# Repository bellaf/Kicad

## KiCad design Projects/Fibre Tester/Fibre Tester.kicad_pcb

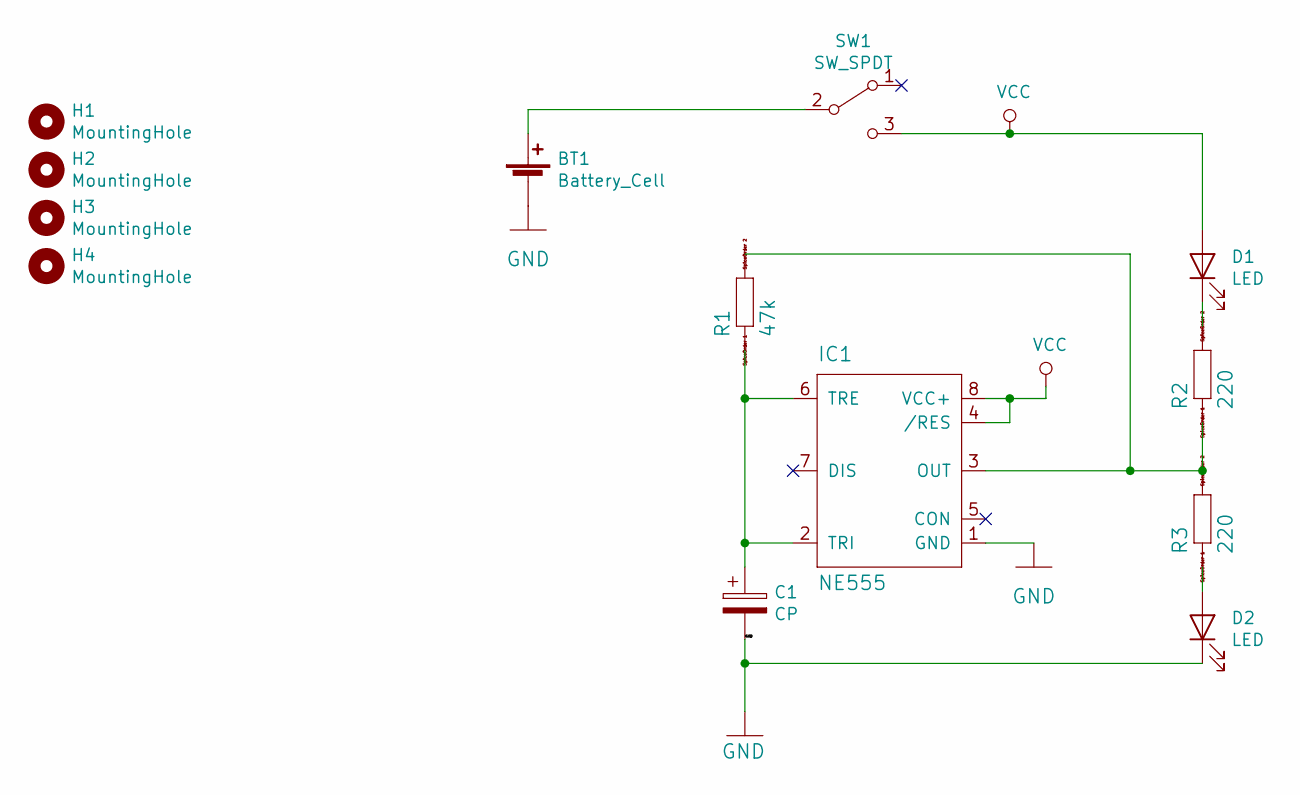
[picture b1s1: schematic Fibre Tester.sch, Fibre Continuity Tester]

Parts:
BT1: Battery_Cell; PinSocket_1x02_P2.54mm_Vertical
C1: CP; CP_Radial_D6.3mm_P2.50mm
D1, D2: LED; LED_D5.0mm_Clear
H1, H2, H3, H4: MountingHole; MountingHole_2.5mm
IC1: NE555; DIP-8_W7.62mm
R1: 47k; R_Axial_DIN0207_L6.3mm_D2.5mm_P10.16mm_Horizontal
R2, R3: 220; R_Axial_DIN0207_L6.3mm_D2.5mm_P10.16mm_Horizontal
SW1: SW_SPDT; SW_Slide_angle_SPDT_TB

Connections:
GND: BT1.2 (-), C1.2, D2.1 (K), IC1.1 (GND)
unnamed: BT1.1 (+), SW1.2 (B)
unnamed: C1.1, IC1.2 (TRI), IC1.6 (TRE), R1.1
unnamed: D1.1 (K), R2.2
unnamed: D2.2 (A), R3.1
unnamed: IC1.3 (OUT), R1.2, R2.1, R3.2
VCC: D1.2 (A), IC1.4 (/RES), IC1.8 (VCC+), SW1.3 (C)

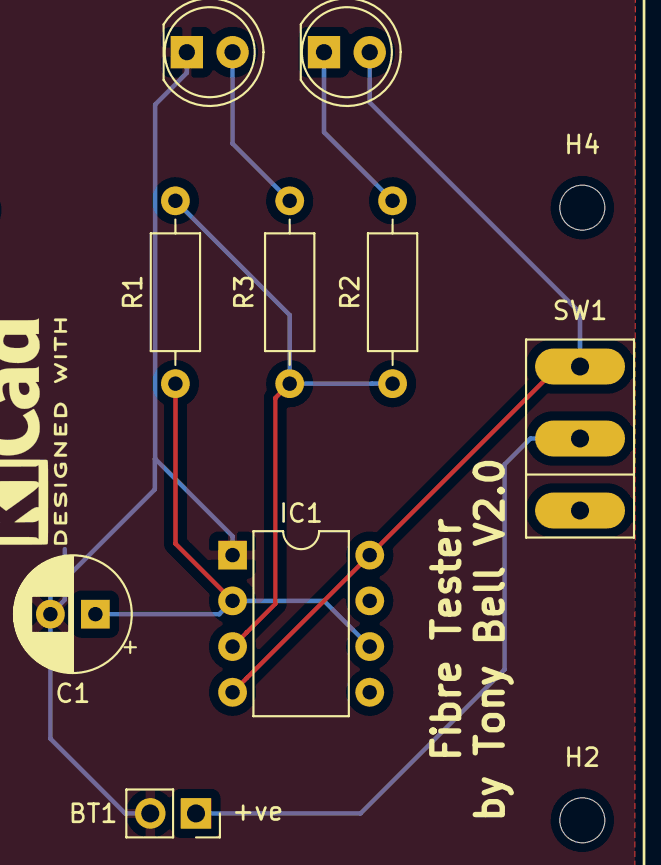
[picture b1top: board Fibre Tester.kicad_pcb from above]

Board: 2 copper layers, 13 parts (0 on the bottom side), 7 nets.

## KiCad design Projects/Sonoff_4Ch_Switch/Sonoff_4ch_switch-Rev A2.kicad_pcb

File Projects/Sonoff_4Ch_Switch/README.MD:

Sonoff inspired, 4Ch Switch using Tasmota Firmware

Notes on implementation

So, configure Tasmota as a HUE Bridge (Multi Device)

Then configure the module as a GENERIC (Type18) module for the Wemos.

Then in the module config, set the following options:

D3 GPIO0: 17 Button1	
TX GPIO1: 00 None	
D4 GPIO2: 18 Button2 	
RX GPIO3: 00 None
D2 GPIO4: 23 Relay3
D1 GPIO5: 22 Relay2 	
D6 GPIO12: 21 Relay1
D7 GPIO13: 00 None
D5 GPIO14: 19 Button3
D8 GPIO15: 24 Relay4
D0 GPIO16: 20 Button4

Thats it, set Alexa to discover it all and bingo!
 	
Adding a DS1820B Onewire connection as well to make the unit versatile......
using GPIO13 on D7 for this..

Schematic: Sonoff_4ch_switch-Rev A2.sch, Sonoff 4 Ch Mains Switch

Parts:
C1: 10uF; CP_Elec_6.3x9.9
C2: 22uF; CP_Elec_6.3x9.9
D9: LED; LED_0805_HandSoldering
F1: Fuse 5A; Fuseholder5x20_horiz_SemiClosed_Casing10x25mm
J1: Barrel_Jack_Switch; BARREL_JACK
J2: Live; TerminalBlock_RND_205-00004_1x05_P5.00mm_Horizontal
J3: Neutrals; TerminalBlock_RND_205-00004_1x05_P5.00mm_Horizontal
J4: Earths; TerminalBlock_RND_205-00004_1x05_P5.00mm_Horizontal
J5: Conn_01x03_Male; PinHeader_1x03_P2.54mm_Vertical
MH1, MH2, MH3, MH4: MountingHole; MountingHole_3mm_Pad
R17, R18, R19, R20, R21: 1K; R_0805_HandSoldering
R22: 4.7K; R_0805_HandSoldering
S1, S2, S3, S4: PTS645SM43SMTR92_LFS; Switch_Tactile_SMD_6x6mm_PTS645; MPN PTS645SM43SMTR92 LFS; Digi-Key_PN CKN9112CT-ND
TP1: 5V; Measurement_Point_Round-SMD-Pad_Small
TP2: 3.3V; TestPoint_Pad_D2.0mm
TP3: GND; Measurement_Point_Round-SMD-Pad_Small
U1: AP1117-50; SOT-223-3_TabPin2
U2: Wemos_D1_Mini_wide; Wemos_D1_mini_board-flipped

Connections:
+3V3: J5.3, R18.1, R19.1, R20.1, R21.1, R22.1, TP2.1, U2.16
+5V: C2.1, R17.1, TP1.1, U1.2 (VO), U2.1; also elsewhere on the board
/DC_IN: C1.1, J1.1, U1.3 (VI)
AC: F1.1, J2.1
Earth: J4.1, J4.2, J4.3, J4.4, J4.5
GND: C1.2, C2.2, D9.1, J1.2, J1.3, J5.1, S1.1, S1.2, S2.1, S2.2, S3.1, S3.2, S4.1, S4.2, TP3.1, U1.1 (GND), U2.2; also elsewhere on the board
L1: J2.2; also elsewhere on the board
L2: J2.3; also elsewhere on the board
L3: J2.4; also elsewhere on the board
L4: J2.5; also elsewhere on the board
LineIN: F1.2; also elsewhere on the board
unnamed: D9.2, R17.2
unnamed: R18.2, S1.3
unnamed: R19.2, S2.3
unnamed: R20.2, S3.3
unnamed: R21.2, S4.3
Neutral: J3.1, J3.2, J3.3, J3.4, J3.5
OneWire: J5.2, R22.2, U2.14
Relay1: U2.13; also elsewhere on the board
Relay2: U2.6; also elsewhere on the board
Relay3: U2.5; also elsewhere on the board
Relay4: U2.15; also elsewhere on the board
SW0: S1.4, U2.4
SW2: S2.4, U2.3
SW14: S3.4, U2.11
SW16: S4.4, U2.12

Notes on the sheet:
PSU: 6V - 12V DC IN (5V Output)
Mains Terminal Blocks
Design notes for rev A2: 1. Add a GND TP, with a pin(?) - Done 2. No Reverse polarity protection 3. Do away with the Regulator? Run it from 5V Power bricks? 4. Redesign the layout with 0805 components! (0603 too small) - Done 5. If keeping the regulator, re-engineer the copper pad for 5V, needs to 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

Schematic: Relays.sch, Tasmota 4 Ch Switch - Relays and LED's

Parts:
D1, D2, D3, D4: 1N4148; D_SOD-123
D5, D6, D7, D8: LED; LED_0805_HandSoldering
K1, K2, K3, K4: G5LE-1; Relay_SPDT_Omron-G5LE-1
Q1, Q2, Q3, Q4, Q5, Q6, Q7, Q8: 2N7002; SOT-23
R1, R3, R5, R7, R9, R10, R11, R12, R13, R14, R15, R16: 1K; R_0805_HandSoldering
R2, R4, R6, R8: 10K; R_0805_HandSoldering

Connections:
+5V: D1.1, D2.1, D3.1, D4.1, D5.2, D6.2, D7.2, D8.2, K1.5, K2.5, K3.5, K4.5; also elsewhere on the board
GND: Q1.2 (S), Q2.2 (S), Q3.2 (S), Q4.2 (S), Q5.2 (S), Q6.2 (S), Q7.2 (S), Q8.2 (S), R2.1, R4.1, R6.1, R8.1; also elsewhere on the board
L1: K1.3; also elsewhere on the board
L2: K2.3; also elsewhere on the board
L3: K3.3; also elsewhere on the board
L4: K4.3; also elsewhere on the board
LineIN: K1.1, K2.1, K3.1, K4.1; also elsewhere on the board
unnamed: D1.2, K1.2, Q1.3 (D)
unnamed: D2.2, K2.2, Q2.3 (D)
unnamed: D3.2, K3.2, Q3.3 (D)
unnamed: D4.2, K4.2, Q4.3 (D)
unnamed: D5.1, R10.2
unnamed: D6.1, R12.2
unnamed: D7.1, R14.2
unnamed: D8.1, R16.2
unnamed: Q1.1 (G), R1.1, R2.2
unnamed: Q2.1 (G), R3.1, R4.2
unnamed: Q3.1 (G), R5.1, R6.2
unnamed: Q4.1 (G), R7.1, R8.2
unnamed: Q5.1 (G), R9.1
unnamed: Q5.3 (D), R10.1
unnamed: Q6.1 (G), R11.1
unnamed: Q6.3 (D), R12.1
unnamed: Q7.1 (G), R13.1
unnamed: Q7.3 (D), R14.1
unnamed: Q8.1 (G), R15.1
unnamed: Q8.3 (D), R16.1
Relay1: R1.2, R9.2; also elsewhere on the board
Relay2: R3.2, R11.2; also elsewhere on the board
Relay3: R5.2, R13.2; also elsewhere on the board
Relay4: R7.2, R15.2; also elsewhere on the board

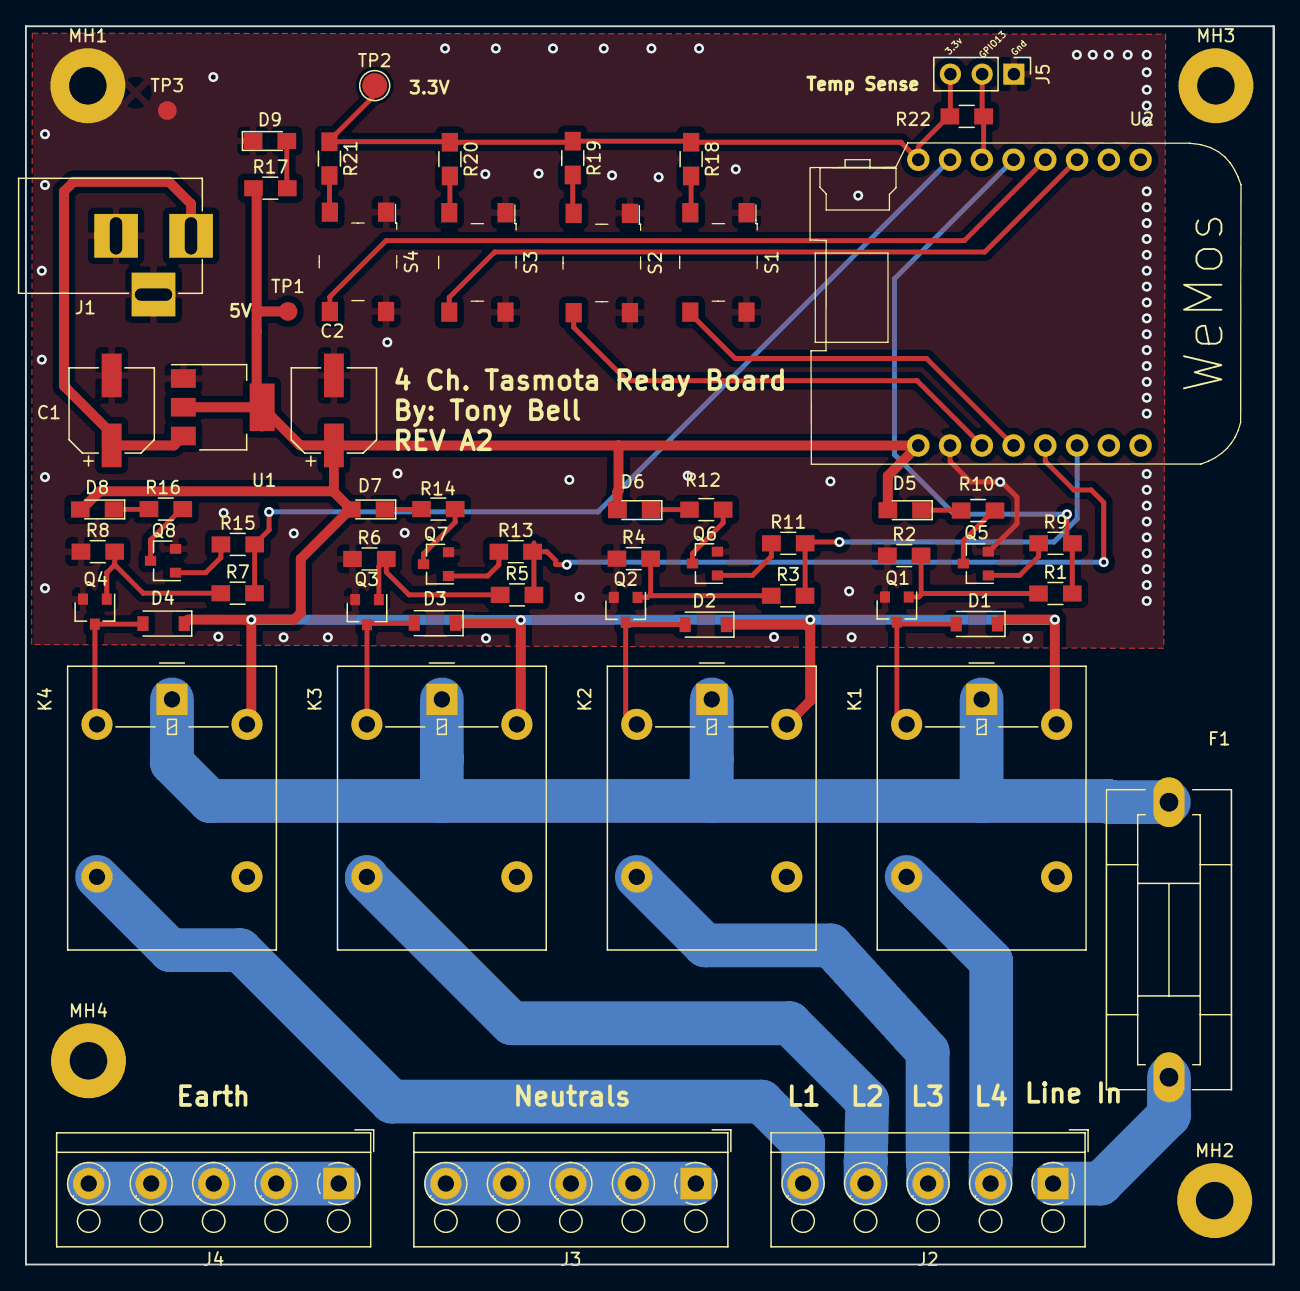
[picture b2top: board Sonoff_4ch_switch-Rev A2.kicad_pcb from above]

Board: 2 copper layers, 99.8 x 99.1 mm, 64 parts (0 on the bottom side), 46 nets.

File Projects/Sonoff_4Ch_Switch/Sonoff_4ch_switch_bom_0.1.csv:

Component,Description,Part,References,Value,Footprint,Quantity Per PCB,Datasheet,Category,Status,Family,MPN,Digi-Key_PN,DK_Datasheet_Link,DK_Detail_Page,Manufacturer
1,Polarised capacitor,CP,C1,10uF,CP_Elec_6.3x9.9,1,,,,,,,,,
2,Polarised capacitor,CP,C2,22uF,CP_Elec_6.3x9.9,1,,,,,,,,,
3,Diode,D,D1 D2 D3 D4,1N4148,D_SOD-123,4,~,,,,,,,,
4,LED generic,LED,D5 D6 D7 D8 D9,LED,LED_0603_HandSoldering,5,~,,,,,,,,
5,"Fuse, generic",Fuse,F1,Fuse 5A,Fuseholder5x20_horiz_SemiClosed_Casing10x25mm,1,~,,,,,,,,
6,DC Barrel Jack with an internal switch,Barrel_Jack_Switch,J1,Barrel_Jack_Switch,BARREL_JACK,1,,,,,,,,,
7,"Generic connector, single row, 01x03, script generated (kicad-library-utils/schlib/autogen/connector/)",Conn_01x03_Male,J5,Conn_01x03_Male,PinHeader_1x03_P2.54mm_Vertical,1,~,,,,,,,,
8,"Generic screw terminal, single row, 01x05, script generated (kicad-library-utils/schlib/autogen/connector/)",Screw_Terminal_01x05,J4,Earths,TerminalBlock_RND_205-00004_1x05_P5.00mm_Horizontal,1,~,,,,,,,,
9,"Generic screw terminal, single row, 01x05, script generated (kicad-library-utils/schlib/autogen/connector/)",Screw_Terminal_01x05,J2,Live,TerminalBlock_RND_205-00004_1x05_P5.00mm_Horizontal,1,~,,,,,,,,
10,"Generic screw terminal, single row, 01x05, script generated (kicad-library-utils/schlib/autogen/connector/)",Screw_Terminal_01x05,J3,Neutrals,TerminalBlock_RND_205-00004_1x05_P5.00mm_Horizontal,1,~,,,,,,,,
11,"Omron G5LE relay, Miniature Single Pole, SPDT, 10A",G5LE-1,K1 K2 K3 K4,G5LE-1,Relay_SPDT_Omron-G5LE-1,4,http://www.omron.com/ecb/products/pdf/en-g5le.pdf,,,,,,,,
12,"50V Vds, 0.22A Id, N-channel MOSFET, SOT-23",2N7002,Q1 Q2 Q3 Q4 Q5 Q6 Q7 Q8,2N7002,SOT-23,8,https://www.fairchildsemi.com/datasheets/2N/2N7002.pdf,,,,,,,,
13,Resistor,R,R2 R4 R6 R8,10K,R_0603_1608Metric_Pad1.05x0.95mm_HandSolder,4,~,,,,,,,,
14,Resistor,R,R1 R3 R5 R7 R9 R10 R11 R12 R13 R14 R15 R16 R17 R18 R19 R20 R21,1K,R_0603_1608Metric_Pad1.05x0.95mm_HandSolder,17,~,,,,,,,,
15,Resistor,R,R22,4.7K,R_0603_1608Metric_Pad1.05x0.95mm_HandSolder,1,~,,,,,,,,
16,SWITCH TACTILE SPST-NO 0.05A 12V,PTS645SM43SMTR92_LFS,S1 S2 S3 S4,PTS645SM43SMTR92_LFS,Switch_Tactile_SMD_6x6mm_PTS645,4,https://www.ckswitches.com/media/1471/pts645.pdf,Switches,Active,Tactile Switches,PTS645SM43SMTR92 LFS,CKN9112CT-ND,https://www.ckswitches.com/media/1471/pts645.pdf,/product-detail/en/c-k/PTS645SM43SMTR92-LFS/CKN9112CT-ND/1146934,C&K
17,1A LDO 5.0V Fixed output,AP1117-50,U1,AP1117-50,SOT-223-3_TabPin2,1,http://www.diodes.com/datasheets/AP1117.pdf,,,,,,,,
18,Wemos D1 Mini with GPIO ports,Wemos_D1_Mini_wide,U2,Wemos_D1_Mini_wide,,1,,,,,,,,,





Component Groups:,18
Component Count:,57
Fitted Components:,57
Number of PCBs:,1
Total components:,57
Schematic Version:,0.1
Schematic Date:,
BoM Date:,08/08/2018 09:17:03
Schematic Source:,C:\Users\BELLAF\Documents\Personal\Electronics Projects\Kicad\Projects\Sonoff_4Ch_Switch\Sonoff_4ch_switch.sch
KiCad Version:,Eeschema (5.0.0)

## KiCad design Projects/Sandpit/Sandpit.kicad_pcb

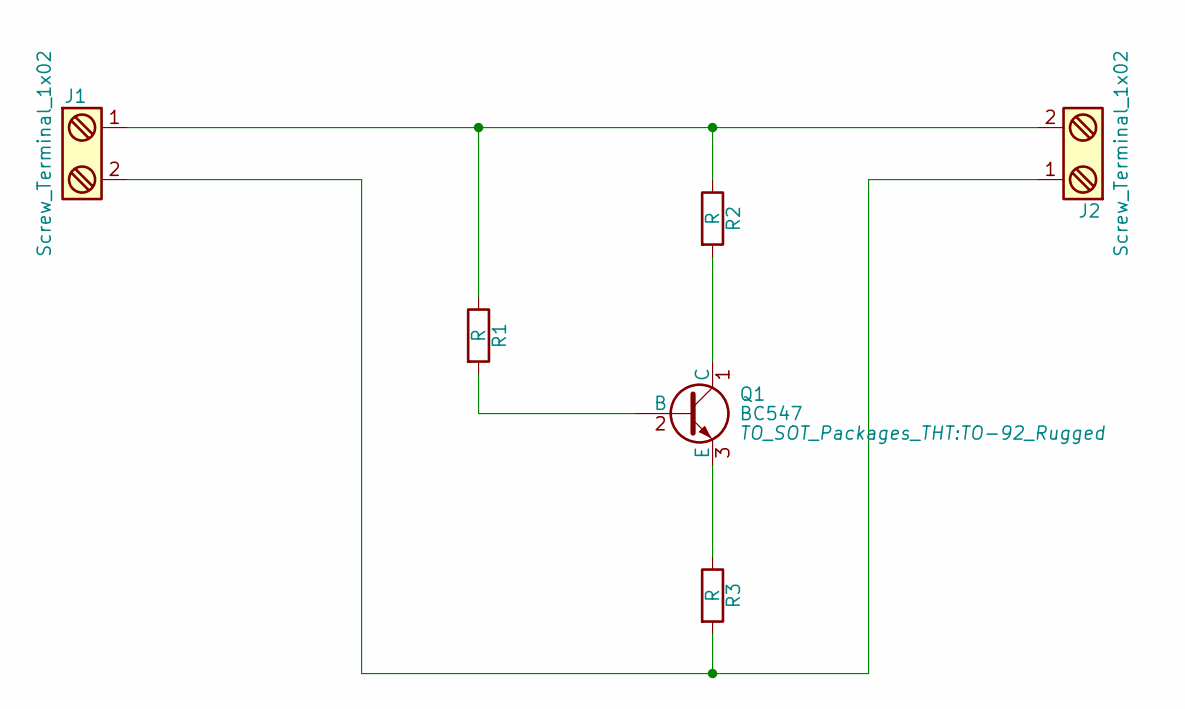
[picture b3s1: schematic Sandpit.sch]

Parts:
J1, J2: Screw_Terminal_1x02; Screw_Terminal_1x02_5mm
Q1: BC547; TO-92_Rugged
R1, R2, R3: R; R_Axial_DIN0207_L6.3mm_D2.5mm_P15.24mm_Horizontal

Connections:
unnamed: J1.1, J2.2, R1.1, R2.1
unnamed: J1.2, J2.1, R3.2
unnamed: Q1.1 (C), R2.2
unnamed: Q1.2 (B), R1.2
unnamed: Q1.3 (E), R3.1

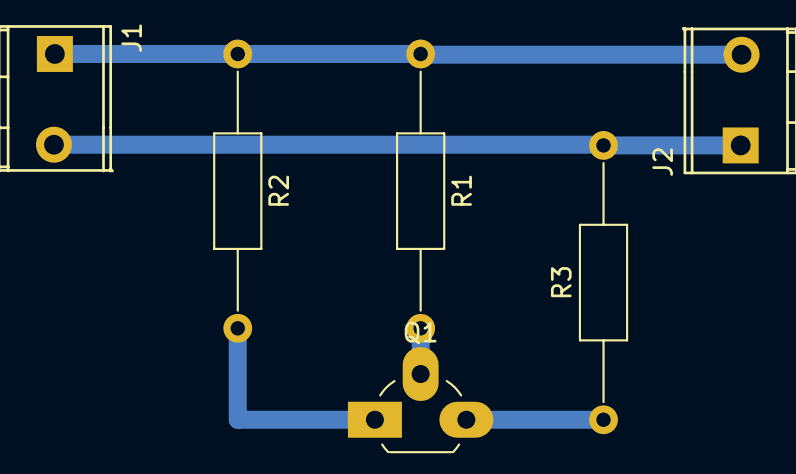
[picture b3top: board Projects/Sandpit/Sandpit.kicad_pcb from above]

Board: 2 copper layers, 6 parts (0 on the bottom side), 5 nets.

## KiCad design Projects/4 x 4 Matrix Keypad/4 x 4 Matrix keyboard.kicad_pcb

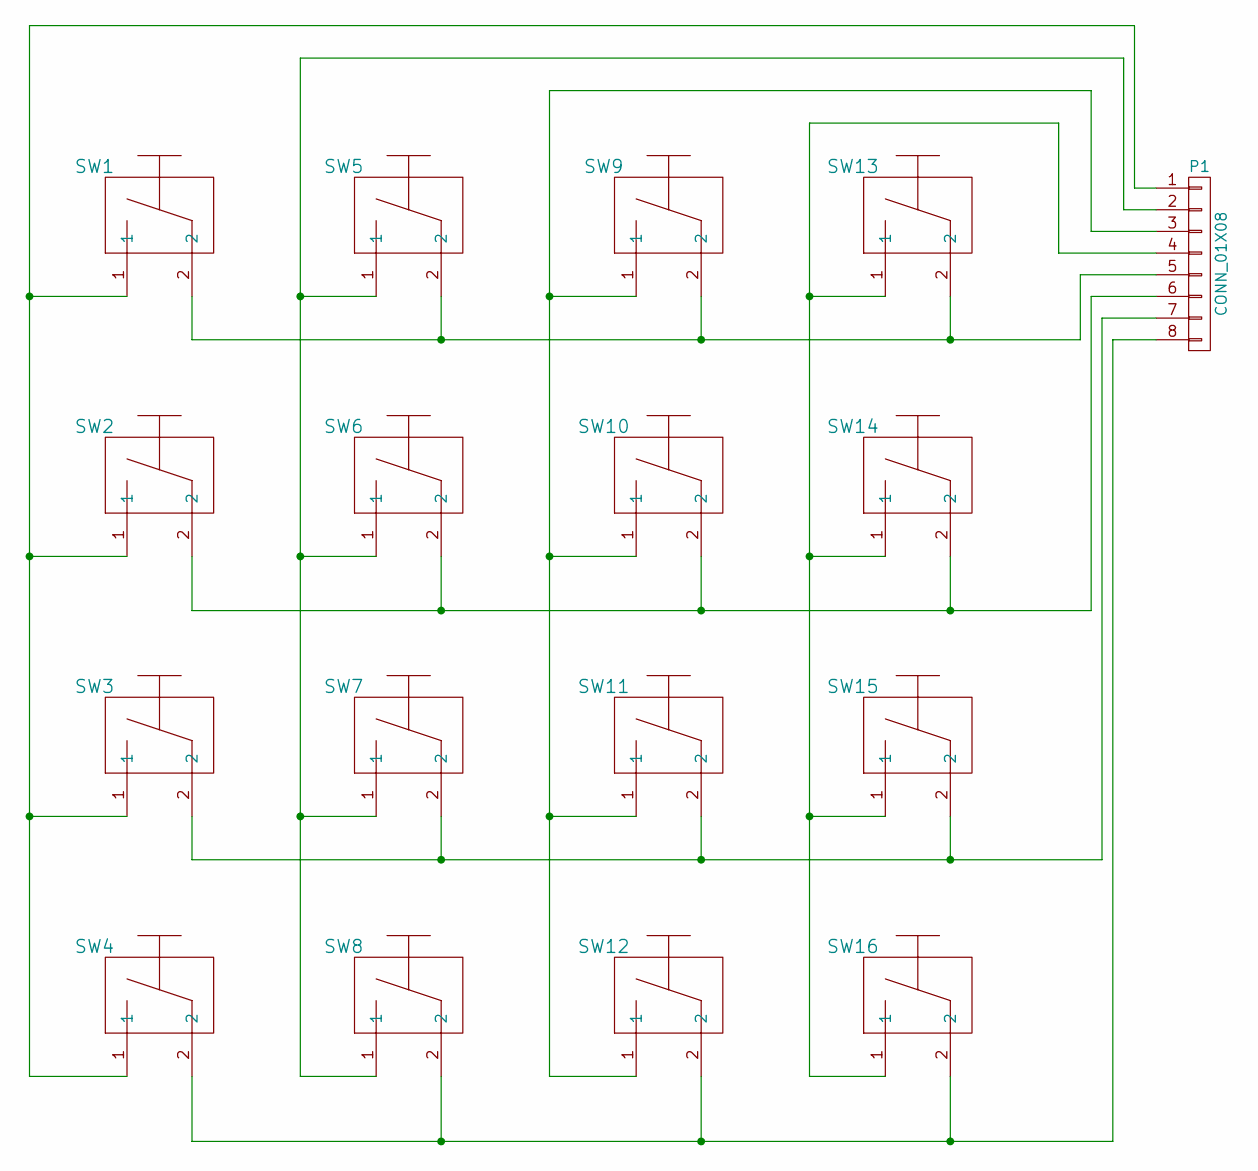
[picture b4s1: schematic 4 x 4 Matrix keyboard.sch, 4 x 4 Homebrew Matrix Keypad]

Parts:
P1: CONN_01X08; Pin_Header_Straight_1x08_Pitch2.54mm
SW1, SW2, SW3, SW4, SW5, SW6, SW7, SW8, SW9, SW10, SW11, SW12, SW14, SW15, SW16: switch_matrix_key; Switch_Matrix_Key_2mm_Pad
SW13: eswitch_matrix_key; Switch_Matrix_Key_2mm_Pad

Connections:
unnamed: P1.1, SW1.1, SW2.1, SW3.1, SW4.1
unnamed: P1.2, SW5.1, SW6.1, SW7.1, SW8.1
unnamed: P1.3, SW9.1, SW10.1, SW11.1, SW12.1
unnamed: P1.4, SW13.1, SW14.1, SW15.1, SW16.1
unnamed: P1.5, SW1.2, SW5.2, SW9.2, SW13.2
unnamed: P1.6, SW2.2, SW6.2, SW10.2, SW14.2
unnamed: P1.7, SW3.2, SW7.2, SW11.2, SW15.2
unnamed: P1.8, SW4.2, SW8.2, SW12.2, SW16.2

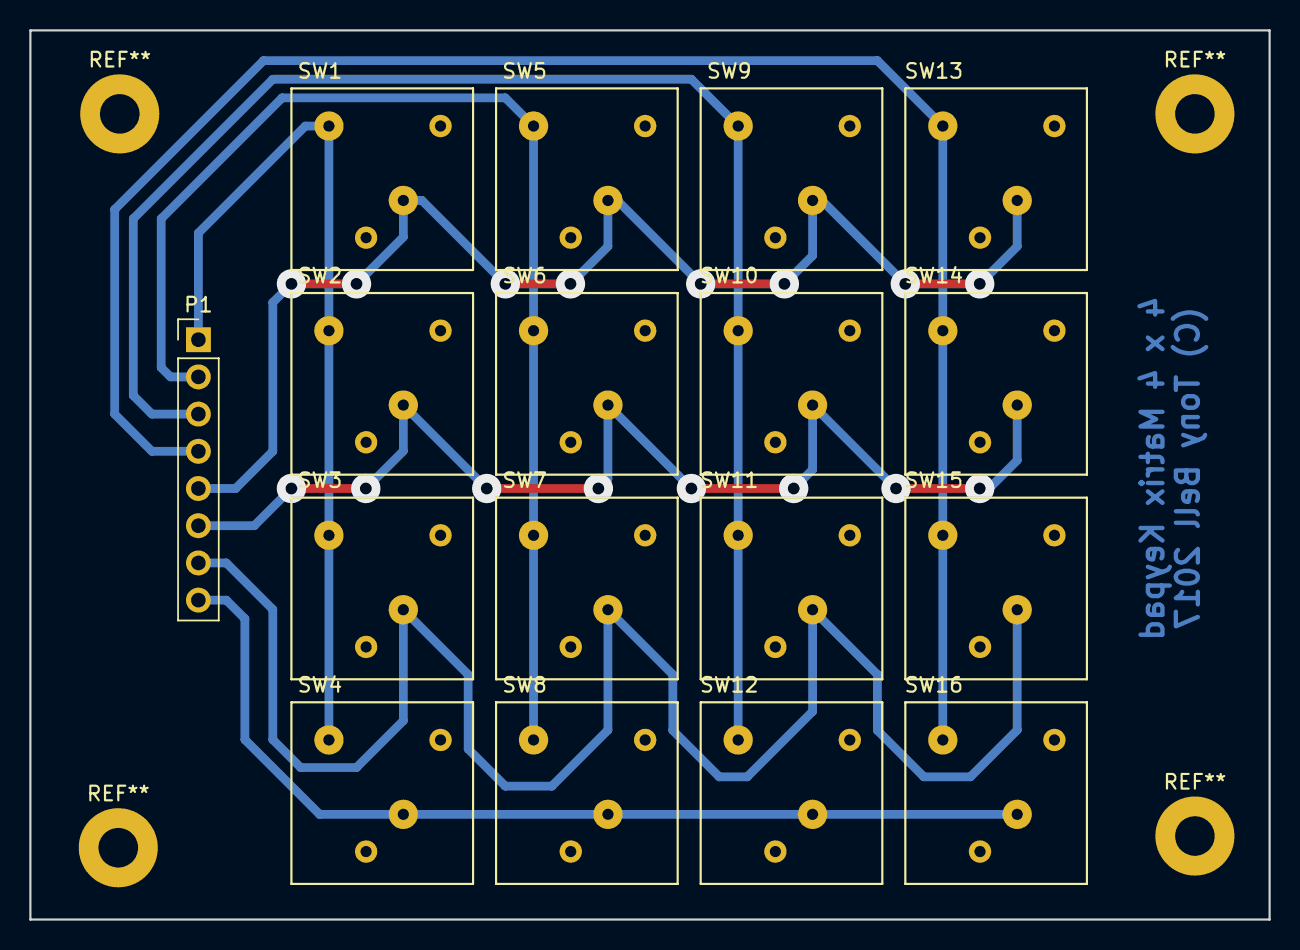
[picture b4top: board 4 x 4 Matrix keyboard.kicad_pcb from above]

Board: 2 copper layers, 84.6 x 60.7 mm, 17 parts (0 on the bottom side), 8 nets.

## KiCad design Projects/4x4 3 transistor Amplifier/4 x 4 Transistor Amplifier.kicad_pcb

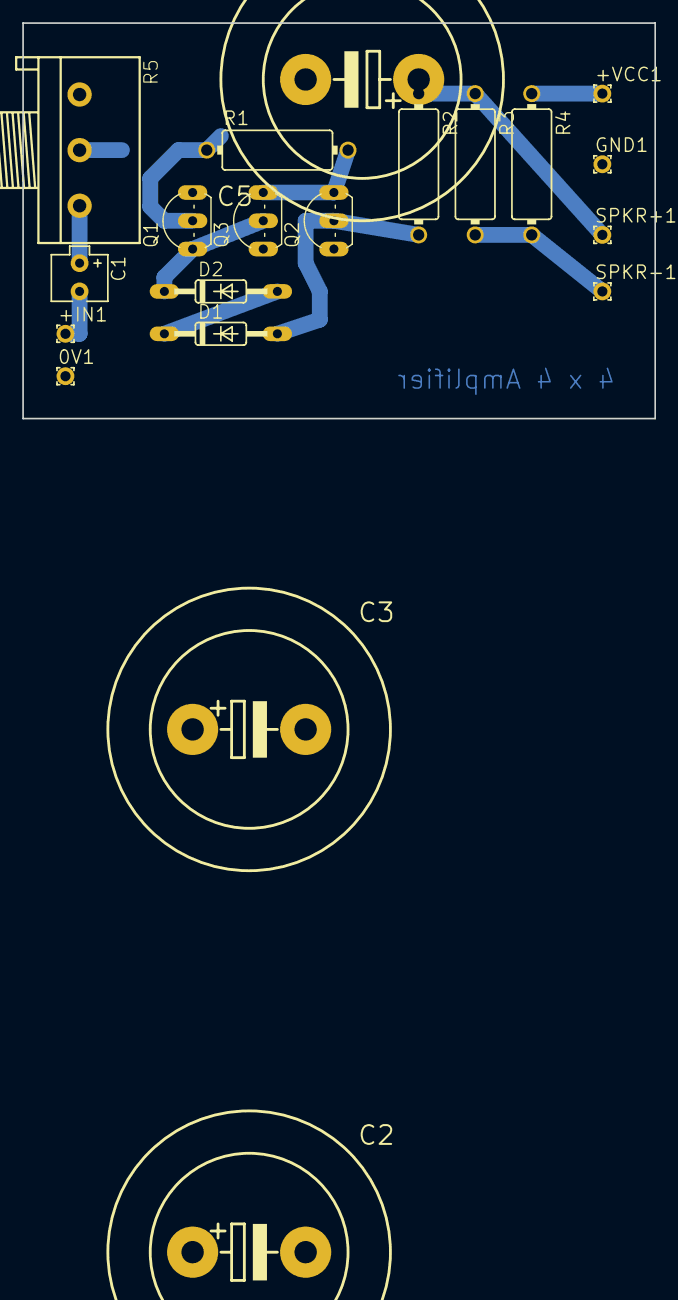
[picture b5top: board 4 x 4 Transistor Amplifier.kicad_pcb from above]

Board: 2 copper layers, 56.8 x 35.5 mm, 20 parts (0 on the bottom side), 12 nets.

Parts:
0V1: 1,6_0,9
+IN1: Sig IN; 1,6_0,9
+VCC1: + VCC; 1,6_0,9
C1: 4.7uf; ETR1
C2, C3, C5: CPOL-EUE10-25; EB25D
D1, D2: 1N4148DO35-10; DO35-10
GND1: -VCC; 1,6_0,9
Q1, Q2: BC549; TO92-EBC
Q3: BC559; TO92-EBC
R1: 100K; V234_12
R2: 220; V234_12
R3: 100; V234_12
R4: 100 (5-12V); V234_12
R5: 100K; 3RP_1610N
SPKR+1: Spkr; 1,6_0,9
SPKR-1: Spkr; 1,6_0,9

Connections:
GND: 0V1.1, C3.-, GND1.1, Q1.E, Q3.C, R5.1
unnamed: +IN1.1, C1.-
unnamed: C1.+, R5.3
unnamed: C2.+, Q1.B, R1.1
unnamed: C2.-, R5.2
unnamed: C3.+, Q2.C, R3.2, R4.2, SPKR-1.1
unnamed: C5.+, R2.1, R3.1, SPKR+1.1
unnamed: C5.-, Q2.E, Q3.E, R1.2
unnamed: D1.A, Q2.B, R2.2
unnamed: D1.C, D2.A
unnamed: D2.C, Q1.C, Q3.B
VCC: +VCC1.1, R4.1

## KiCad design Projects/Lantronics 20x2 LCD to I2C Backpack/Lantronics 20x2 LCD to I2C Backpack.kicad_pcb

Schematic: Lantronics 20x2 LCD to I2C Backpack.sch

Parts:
C1: 0.1uF; C_Rect_L7.0mm_W2.5mm_P5.00mm
D1: LED; LED_D3.0mm
DS1: LCD16X2; Pin_Header_Angled_2x08_Pitch2.54mm
P1: CONN_01X04; Pin_Header_Straight_1x04_Pitch2.54mm
P2: CONN_01X02; Pin_Header_Straight_1x02_Pitch2.54mm
Q1: BC817-40; TO-92_Inline_Wide
R1: 220R; R_Axial_DIN0204_L3.6mm_D1.6mm_P5.08mm_Horizontal
R2, R3, R7: 4.7K; R_Axial_DIN0204_L3.6mm_D1.6mm_P5.08mm_Horizontal
R4, R5, R6: Short; R_Axial_DIN0204_L3.6mm_D1.6mm_P2.54mm_Vertical
RV1: 10K; Potentiometer_Trimmer_Piher_PT-6v_Horizontal
U1: PCF8574; DIP-16_W7.62mm

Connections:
/LED-: DS1.16 (LED-), Q1.3 (C)
GND: C1.2, D1.1, DS1.1 (VSS), P1.1, Q1.2 (E), R4.2, R5.2, R6.2, RV1.3, U1.8 (VSS)
LED+: DS1.15 (LED+), P2.1
unnamed: D1.2, R1.1
unnamed: DS1.4 (RS), U1.4 (P0)
unnamed: DS1.5 (R/W), U1.5 (P1)
unnamed: DS1.6 (E), U1.6 (P2)
unnamed: DS1.11 (D4), U1.9 (P4)
unnamed: DS1.12 (D5), U1.10 (P5)
unnamed: DS1.13 (D6), U1.11 (P6)
unnamed: DS1.14 (D7), U1.12 (P7)
unnamed: P1.3, R2.2, U1.14 (SCL)
unnamed: P1.4, R3.2, U1.15 (SDA)
unnamed: Q1.1 (B), R7.2, U1.7 (P3)
unnamed: R4.1, U1.1 (A0)
unnamed: R5.1, U1.2 (A1)
unnamed: R6.1, U1.3 (A2)
VCC: C1.1, DS1.2 (VDD), P1.2, P2.2, R1.2, R2.1, R3.1, R7.1, RV1.1, U1.16 (VDD)
VO: DS1.3 (VO), RV1.2

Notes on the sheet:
Power
Backlight Enable

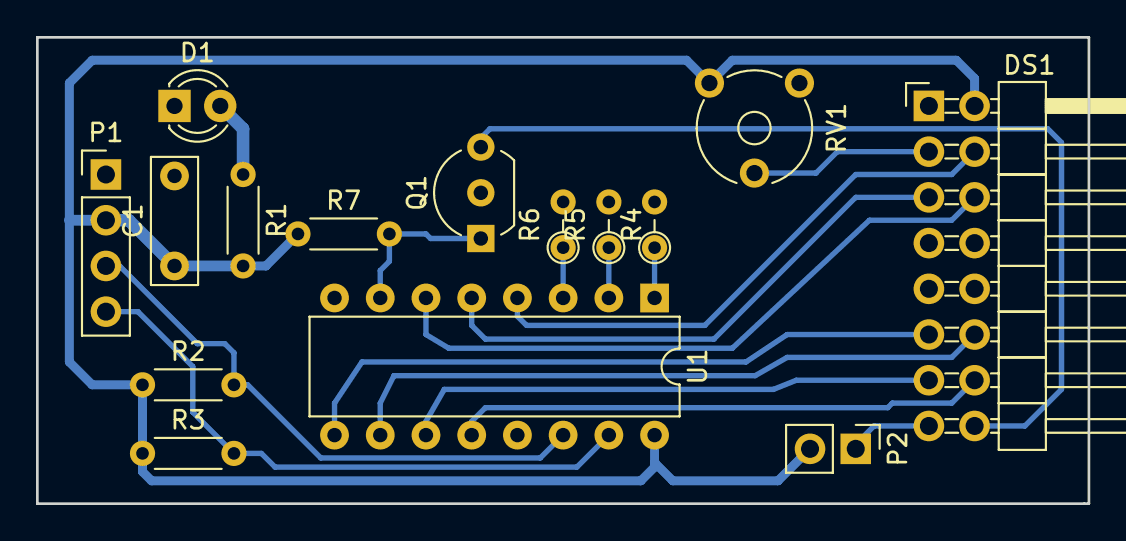
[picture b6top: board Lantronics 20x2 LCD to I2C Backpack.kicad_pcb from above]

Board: 2 copper layers, 58.4 x 25.9 mm, 15 parts (0 on the bottom side), 19 nets.

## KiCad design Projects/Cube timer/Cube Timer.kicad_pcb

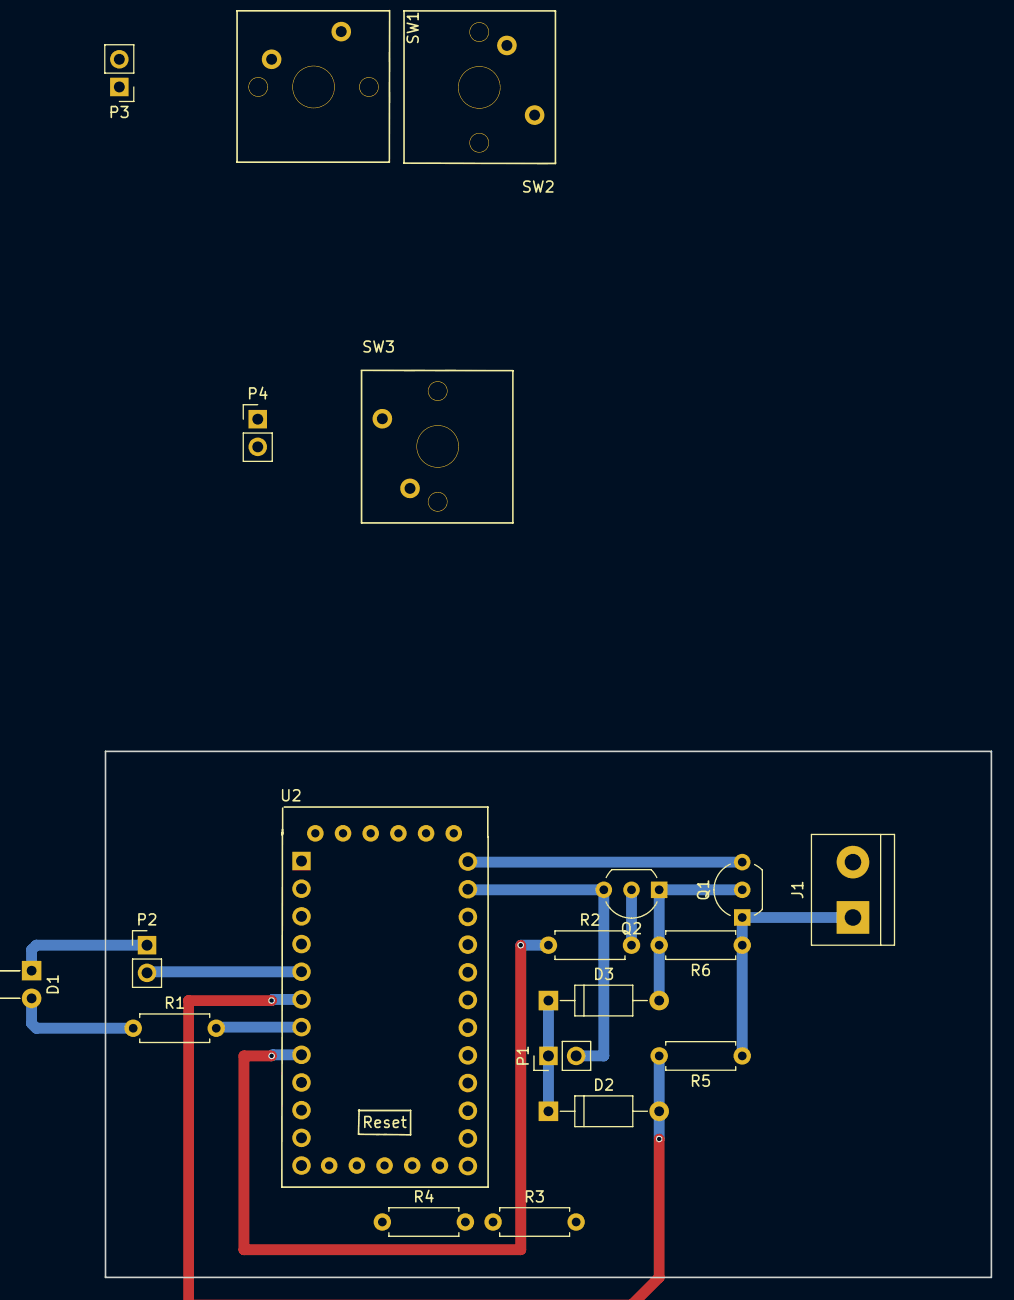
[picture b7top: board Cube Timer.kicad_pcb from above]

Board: 2 copper layers, 20 parts (0 on the bottom side), 19 nets.

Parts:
D1: LED; LED_D5.0mm_Horizontal_O6.35mm_Z9.0mm
D2, D3: 1N4001; D_A-405_P10.16mm_Horizontal
J1: Screw_Terminal_1x02; bornier2
P1, P2, P3, P4: CONN_01X02; Pin_Header_Straight_1x02_Pitch2.54mm
Q1: ZVP3306A-P-MOSFET; TO-92_Inline_Wide
Q2: BC547; TO-92_Inline_Wide
R1: R; R_Axial_DIN0207_L6.3mm_D2.5mm_P7.62mm_Horizontal
R2, R3, R4: 10K; R_Axial_DIN0207_L6.3mm_D2.5mm_P7.62mm_Horizontal
R5, R6: 100K; R_Axial_DIN0207_L6.3mm_D2.5mm_P7.62mm_Horizontal
SW1, SW2, SW3: switch_matrix_key; Keyboard-Tactile-Switch
U2: ArduinoProMini; Arduino_Pro_Mini

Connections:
Batt+: Q1.3, U2.29
unnamed: D1.2, R1.1
unnamed: D2.1, D3.1, P1.1
unnamed: D3.2, Q1.2, Q2.1, R6.2
unnamed: R3.2, U2.15
unnamed: R4.2, U2.14
unnamed: P2.2, U2.5
unnamed: P3.1, SW2.1
unnamed: P3.2, SW1.2
unnamed: P4.1, SW3.1
unnamed: P4.2, SW3.2
unnamed: Q2.2, R2.2
unnamed: R1.2, U2.7
unnamed: SW1.1, SW2.2
Out+: J1.1, Q1.1, R5.1, R6.1
Out-: D1.1, J1.2, P1.2, P2.1, Q2.3, U2.13, U2.28
Reset: D2.2, R5.2, U2.6
StayOn: R2.1, U2.8
VCC: R3.1, R4.1, U2.26

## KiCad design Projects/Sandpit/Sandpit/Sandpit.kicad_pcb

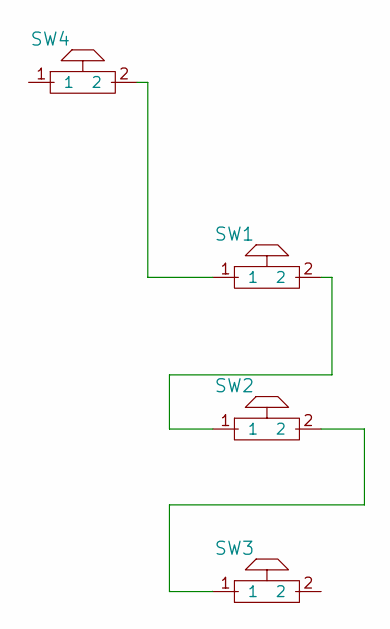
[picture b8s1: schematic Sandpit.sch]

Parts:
SW1, SW2, SW3, SW4: switch_matrix_key; Keyboard-Tactile-Switch

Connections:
unnamed: SW1.1, SW4.2
unnamed: SW1.2, SW2.1
unnamed: SW2.2, SW3.1

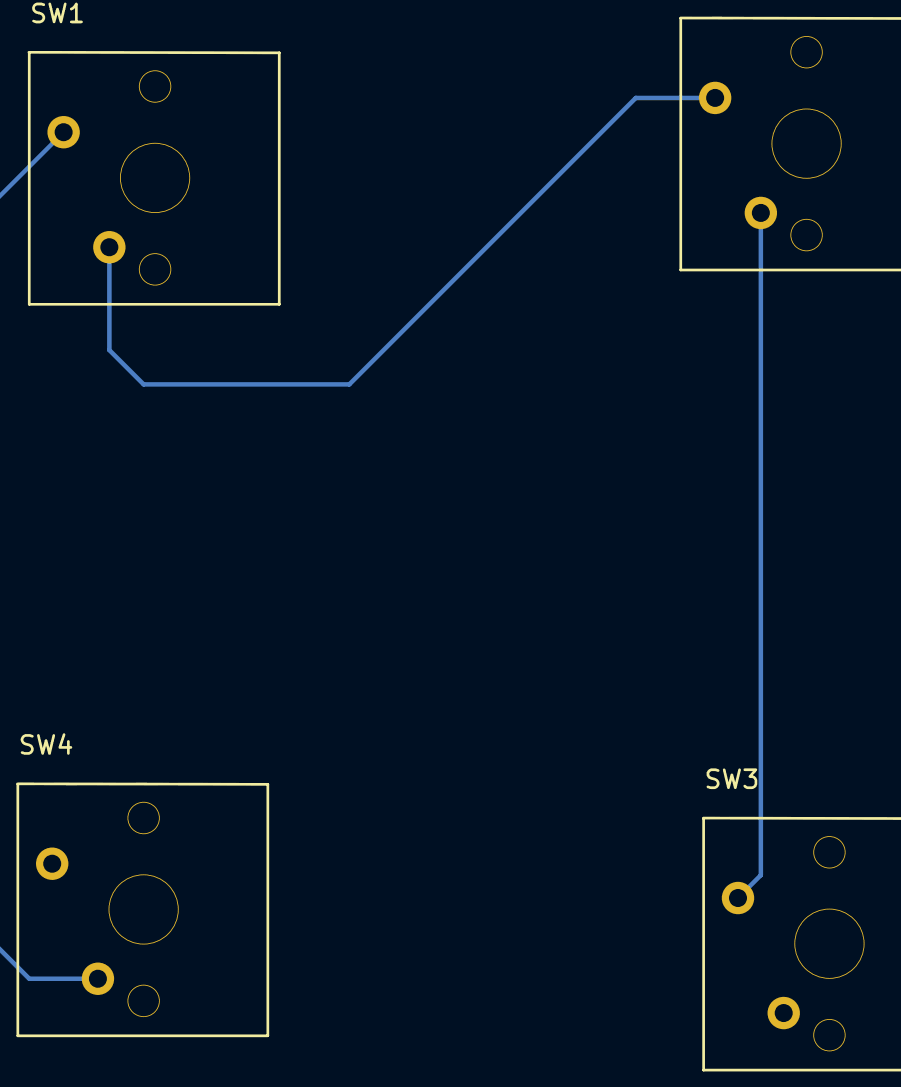
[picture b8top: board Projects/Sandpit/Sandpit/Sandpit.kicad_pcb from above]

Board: 2 copper layers, 4 parts (0 on the bottom side), 3 nets.

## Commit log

2018-08-08 Initial commit of all Kicad stuff
2018-08-08 Added all home based projects...
2018-08-09 Added some Build notes comments about the Reset to defaults issue
2018-08-09 Added notes to Build info for Sonoff switch
2018-08-14 On to rev A2 of the 4 ch switch....
2018-09-05 Created new 2Ch Tasmota Switch
2018-09-06 SOrted out 2Ch layout, condensed into a single SCH sheet
2019-04-25 new file: Libraries/My_Component_Footprints.pretty/Switch_Slide_3_way_pad_SMD.kicad_mod modified: Projects/Fibre Tester/Fibre Tester-cache.lib renamed: Projects/Fibre Tester/Fibre_Tester-eagle-import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
2019-06-14 Updated Fibre Tester project
2019-06-14 Updated footprint files
2019-06-14 Ammended overall PCB size to Fibre tester and ccreated Gerbers
